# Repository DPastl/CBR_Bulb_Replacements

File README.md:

CBR_Bulb_Replacements
=====================

CBR250R Bulb Replacements

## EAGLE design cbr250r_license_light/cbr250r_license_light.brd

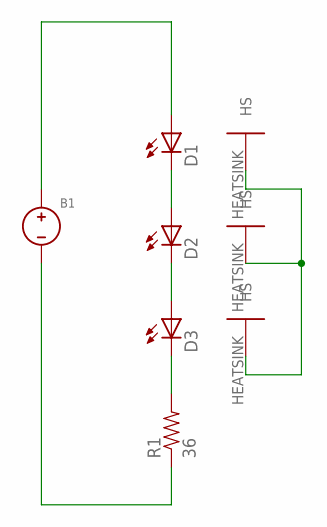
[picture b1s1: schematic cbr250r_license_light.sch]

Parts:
B1: 168_BULBLIGHT_DOWN; 168_BULB
D1, D2, D3: LED_HEATSINK4-SMD; 4-SMD
R1: 36; R2010

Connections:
GND: B1.2A (-), B1.2B (-), R1.1
HEATSINK: D1.HEATSINK (HS), D2.HEATSINK (HS), D3.HEATSINK (HS)
unnamed: D1.CAT1 (C), D1.CAT2 (C), D2.ANO1 (A), D2.ANO2 (A)
unnamed: D2.CAT1 (C), D2.CAT2 (C), D3.ANO1 (A), D3.ANO2 (A)
unnamed: D3.CAT1 (C), D3.CAT2 (C), R1.2
VDD: B1.1A (+), B1.1B (+), D1.ANO1 (A), D1.ANO2 (A)

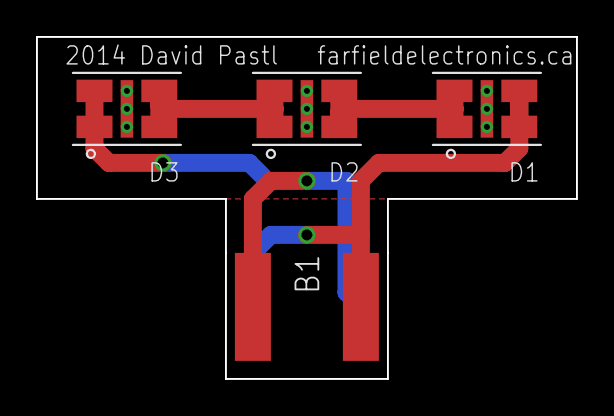
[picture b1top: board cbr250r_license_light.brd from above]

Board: 2 copper layers, 30.0 x 19.0 mm, 5 parts (1 on the bottom side), 6 nets.

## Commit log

2014-08-22 First commit. This version was sent to manufacturing today.

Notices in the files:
parts and their libraries:
SparkFun-Passives: Licensing: Creative Commons ShareAlike 4.0 International - https://creativecommons.org/licenses/by-sa/4.0
